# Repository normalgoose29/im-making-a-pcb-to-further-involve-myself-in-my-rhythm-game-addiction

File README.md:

# pcb
 im making more stuff for my addiction

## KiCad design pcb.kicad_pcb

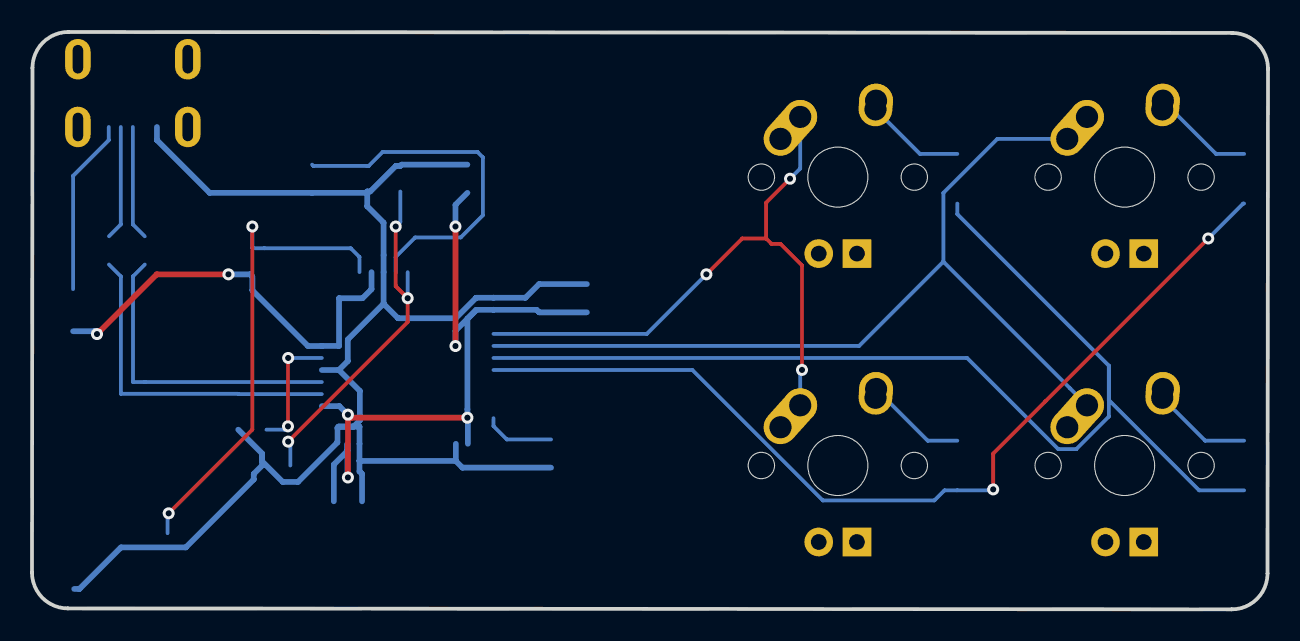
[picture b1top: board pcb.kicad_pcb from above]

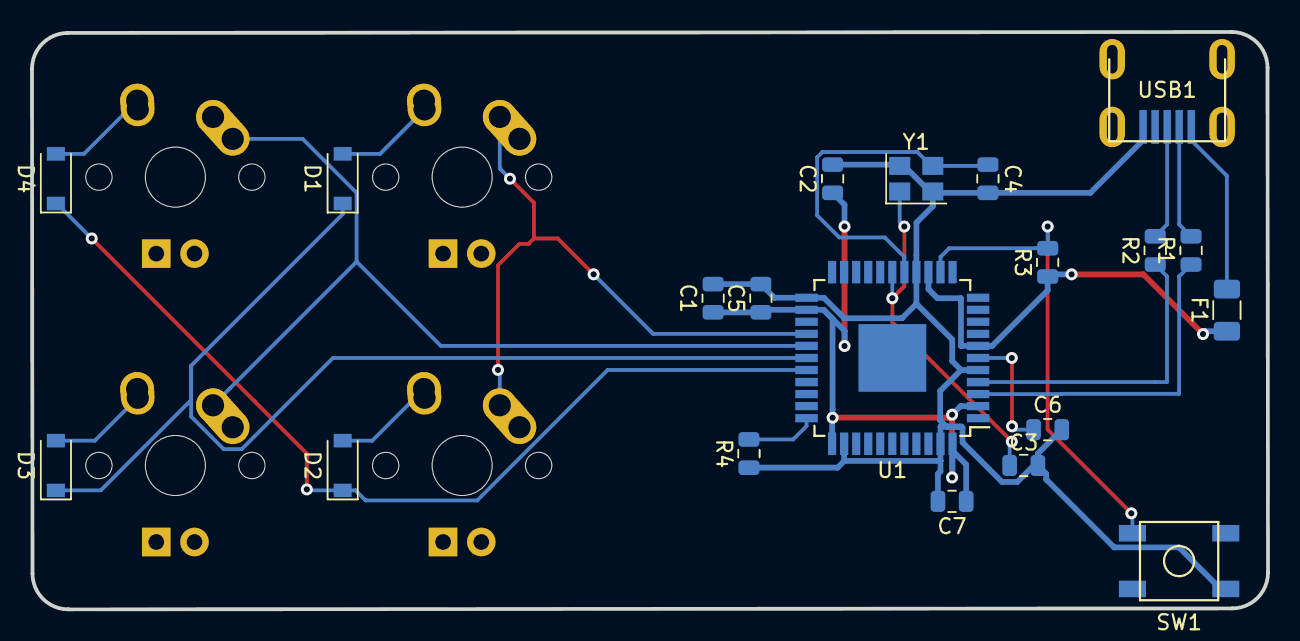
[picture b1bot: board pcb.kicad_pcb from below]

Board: 2 copper layers, 82.1 x 38.4 mm, 24 parts (20 on the bottom side), 20 nets.

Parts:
C1, C2, C5, C6, C7: 1uF; C_0805_2012Metric
C3, C4: 22pF; C_0805_2012Metric
D1, D2, D3, D4: D_Small; D_SOD-123
F1: 500mA; Fuse_1206_3216Metric
MX1, MX2, MX3, MX4: MX-NoLED; MX-1U
R1, R2: 22; R_0805_2012Metric
R3, R4: 10k; R_0805_2012Metric
SW1: SW_Push; SKQG-1155865
U1: ATmega32U4-AU; TQFP-44-1EP_10x10mm_P0.8mm_EP4.5x4.5mm
USB1: Molex-0548190589
Y1: Crystal_GND24_Small; Crystal_SMD_3225-4Pin_3.2x2.5mm

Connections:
+5V: C1.1, C2.1, C5.1, C7.1, F1.1, R3.1, U1.2, U1.7, U1.14, U1.24, U1.34, U1.44
COL0: MX1.1, MX2.1, U1.26
COL1: MX3.1, MX4.1, U1.27
D+: R2.2, USB1.3
D-: R1.2, USB1.4
GND: C1.2, C2.2, C3.2, C4.2, C5.2, C6.2, C7.2, R4.1, SW1.1, U1.5, U1.15, U1.23, U1.35, U1.43, USB1.1, Y1.2, Y1.4
unnamed: C3.1, U1.17, Y1.1
unnamed: C4.1, Y1.3
unnamed: C6.1, U1.6
unnamed: D1.2, MX1.2
unnamed: D2.2, MX2.2
unnamed: D3.2, MX3.2
unnamed: D4.2, MX4.2
unnamed: R1.1, U1.3
unnamed: R2.1, U1.4
unnamed: R3.2, SW1.2, U1.13
unnamed: R4.2, U1.33
ROW0: D1.1, D3.1, U1.28
ROW1: D2.1, D4.1, U1.29
VCC: F1.2, USB1.5

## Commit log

2022-09-03 add submodules
2022-09-03 committed
2022-09-04 blahblahblah
2022-09-04 peepeepoopooo
